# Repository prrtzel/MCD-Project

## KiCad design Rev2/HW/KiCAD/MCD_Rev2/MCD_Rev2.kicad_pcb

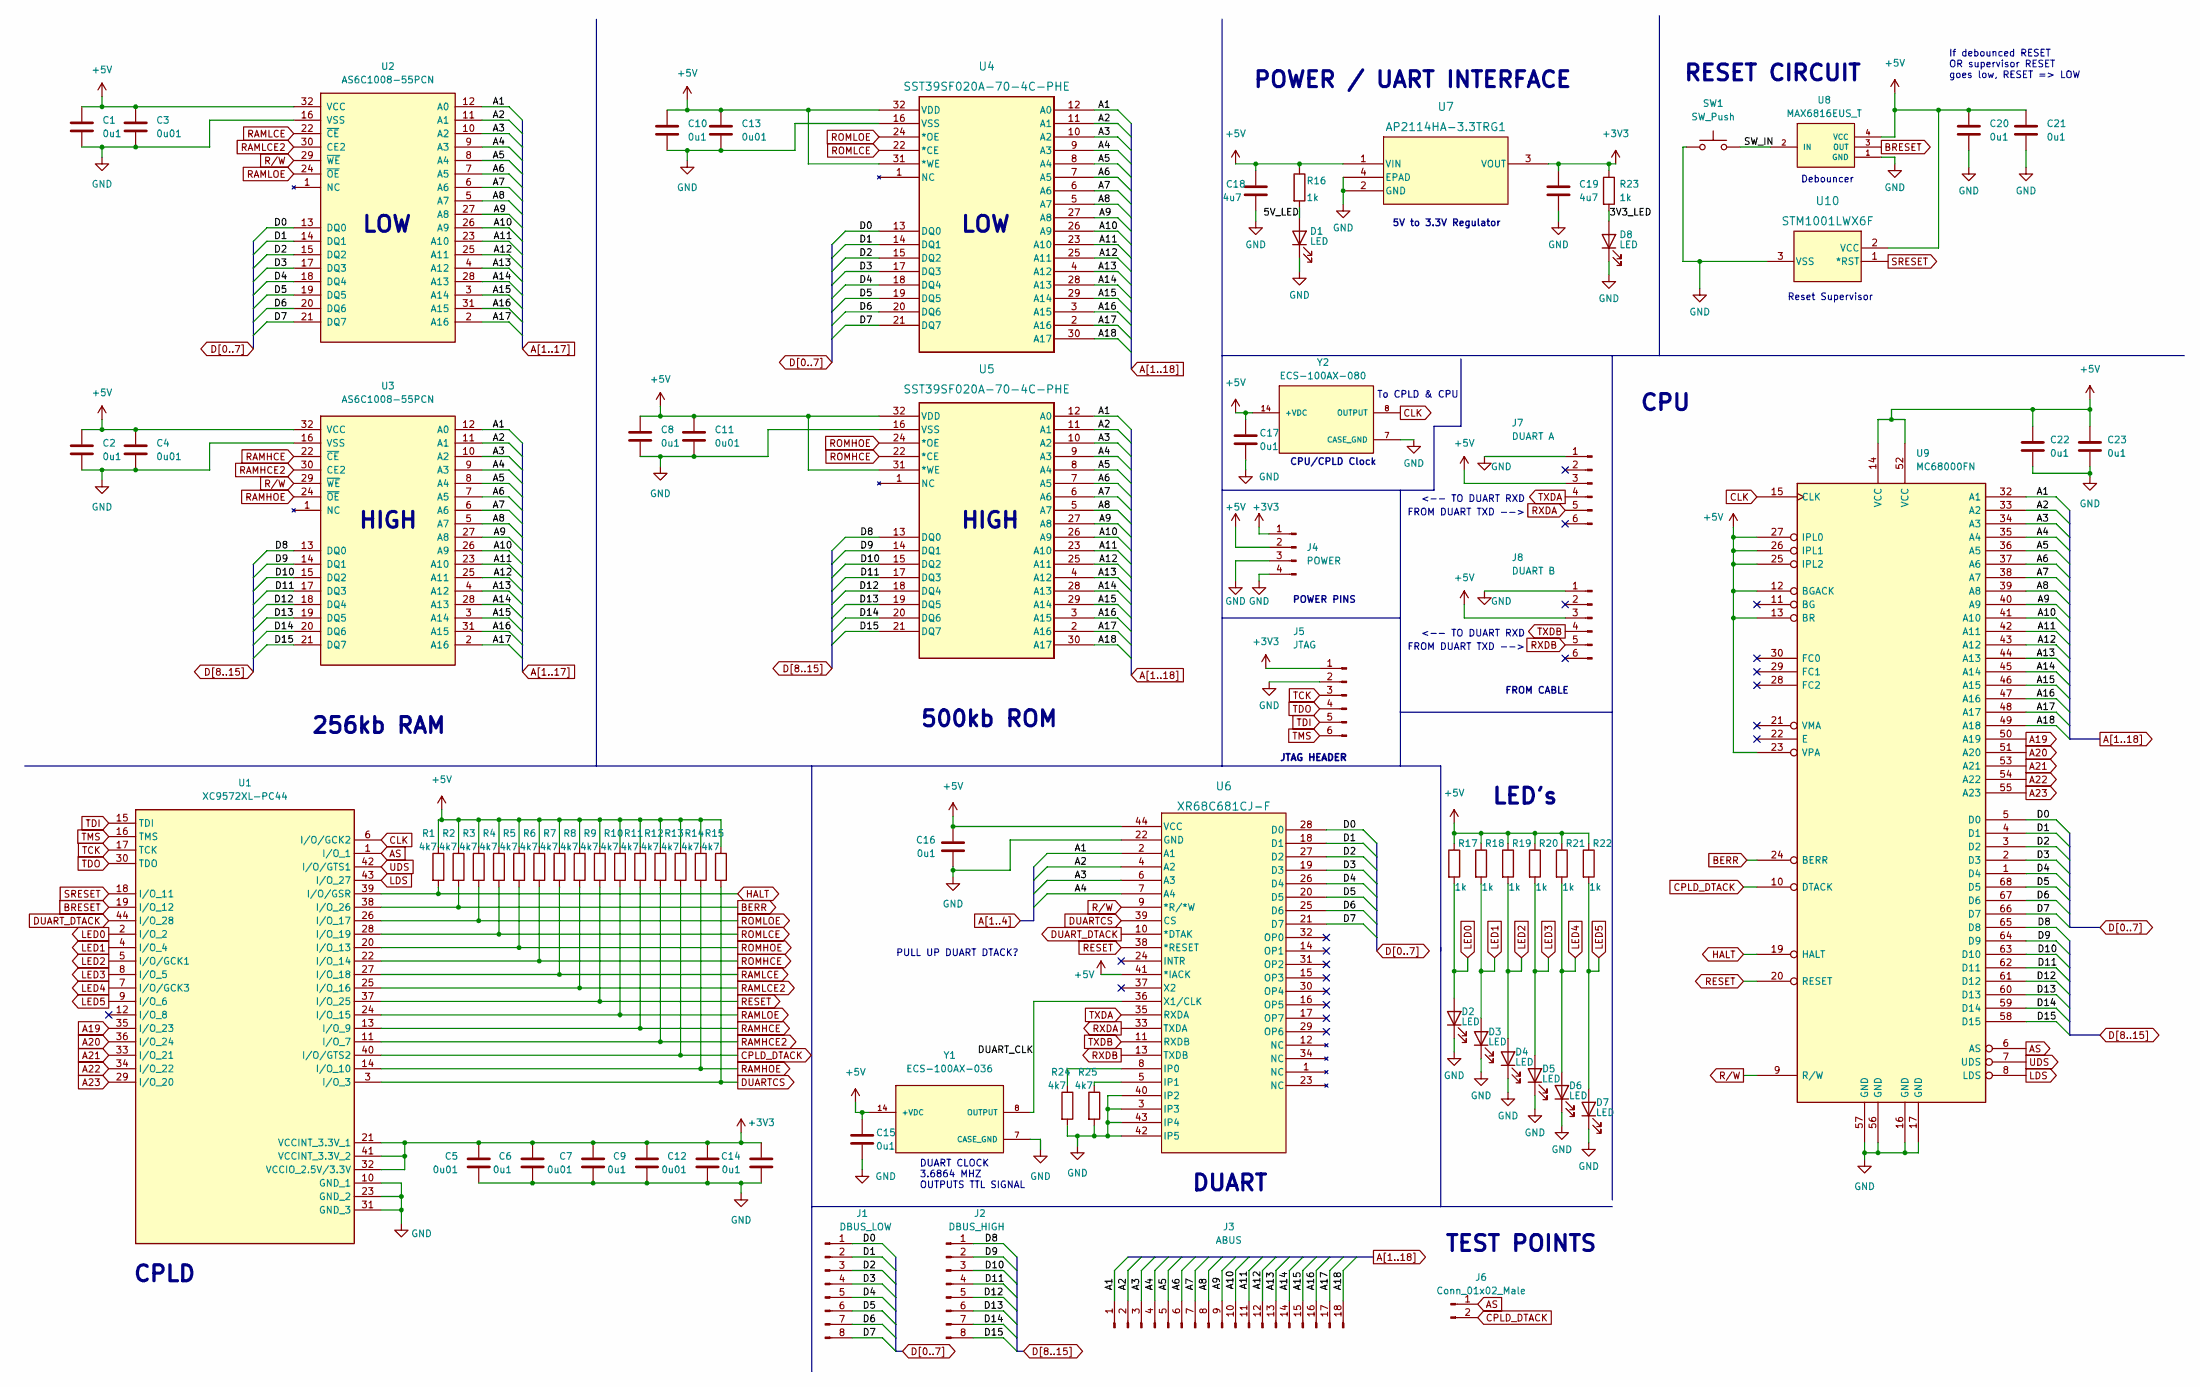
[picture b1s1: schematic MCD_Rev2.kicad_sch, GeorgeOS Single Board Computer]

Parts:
C1, C2, C6, C8, C9, C10, C14, C15, C16, C17, C20, C21, C22, C23: 0u1; C_0805_2012Metric_Pad1.18x1.45mm_HandSolder
C3, C4, C5, C7, C11, C12, C13: 0u01; C_0805_2012Metric_Pad1.18x1.45mm_HandSolder
C18, C19: 4u7; C_0805_2012Metric_Pad1.18x1.45mm_HandSolder
D1, D2, D3, D4, D5, D6, D7, D8: LED; LED_0805_2012Metric_Pad1.15x1.40mm_HandSolder
J1: DBUS_LOW; CON8_1X8_TU_HTS_SAI
J2: DBUS_HIGH; CON8_1X8_TU_HTS_SAI
J3: ABUS; CON18_2X9_TU_HTS_SAI
J4: POWER; CON4_1X4_TU_HTS_SAI
J5: JTAG; CON6_1X6_TU_HTS_SAI
J6: Conn_01x02_Male; CON2_1X2_TU_HTS_SAI
J7: DUART A; CON6_1X6_TU_HTS_SAI
J8: DUART B; CON6_1X6_TU_HTS_SAI
R1, R2, R3, R4, R5, R6, R7, R8, R9, R10, R11, R12, R13, R14, R15, R24, R25: 4k7; R_0805_2012Metric_Pad1.20x1.40mm_HandSolder
R16, R17, R18, R19, R20, R21, R22, R23: 1k; R_0805_2012Metric_Pad1.20x1.40mm_HandSolder
SW1: SW_Push; SW_PUSH_6mm
U1: XC9572XL-PC44; TO_11B1-RK-TP_3MM
U2, U3: AS6C1008-55PCN; PDIP32_PH_SST_MCH; PARTREV v1.0
U4, U5: SST39SF020A-70-4C-PHE; PDIP32_PH_SST_MCH
U6: XR68C681CJ-F; TO_11B1-RK-TP_3MM
U7: AP2114HA-3.3TRG1; SOT-223_DIO-L
U8: MAX6816EUS_T; SOT-143_Handsoldering
U9: MC68000FN; 3M_8468-11B1-RK-TP
U10: STM1001LWX6F; SOT-23_STM-L
Y1: ECS-100AX-036; OSC_ECS-100AX-036
Y2: ECS-100AX-080; OSC_ECS-100AX-080

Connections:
+3V3: C5.1, C6.1, C7.1, C9.1, C12.1, C14.1, C19.1, J4.1, J5.1, R23.1, U1.21 (VCCINT_3.3V_1), U1.32 (VCCIO_2.5V/3.3V), U1.41 (VCCINT_3.3V_2), U7.3 (VOUT)
+5V: C1.1, C2.1, C3.1, C4.1, C8.1, C10.1, C11.1, C13.1, C15.1, C16.1, C17.1, C18.1, C20.1, C21.1, C22.1, C23.1, J4.2, J7.3, J8.3, R1.1, R2.1, R3.1, R4.1, R5.1, R6.1, R7.1, R8.1, R9.1, R10.1, R11.1, R12.1, R13.1, R14.1, R15.1, R16.1, R17.1, R18.1, R19.1, R20.1, R21.1, R22.1, U2.32 (VCC), U3.32 (VCC), U4.31 (*WE), U4.32 (VDD), U5.31 (*WE), U5.32 (VDD), U6.41 (*IACK), U6.44 (VCC), U7.1 (VIN), U8.4 (VCC), U9.12 (BGACK), U9.13 (BR), U9.14 (VCC), U9.23 (VPA), U9.25 (IPL2), U9.26 (IPL1), U9.27 (IPL0), U9.52 (VCC), U10.2 (VCC), Y1.14 (+VDC), Y2.14 (+VDC)
/3V3_LED: D8.2 (A), R23.2
/5V_LED: D1.2 (A), R16.2
/DUART_CLK: U6.36 (X1/CLK), Y1.8 (OUTPUT)
/SW_IN: SW1.2, U8.2 (IN)
A1: J3.1, U2.12 (A0), U3.12 (A0), U4.12 (A0), U5.12 (A0), U6.2 (A1), U9.32 (A1)
A2: J3.2, U2.11 (A1), U3.11 (A1), U4.11 (A1), U5.11 (A1), U6.4 (A2), U9.33 (A2)
A3: J3.3, U2.10 (A2), U3.10 (A2), U4.10 (A2), U5.10 (A2), U6.6 (A3), U9.34 (A3)
A4: J3.4, U2.9 (A3), U3.9 (A3), U4.9 (A3), U5.9 (A3), U6.7 (A4), U9.35 (A4)
A5: J3.5, U2.8 (A4), U3.8 (A4), U4.8 (A4), U5.8 (A4), U9.36 (A5)
A6: J3.6, U2.7 (A5), U3.7 (A5), U4.7 (A5), U5.7 (A5), U9.37 (A6)
A7: J3.7, U2.6 (A6), U3.6 (A6), U4.6 (A6), U5.6 (A6), U9.38 (A7)
A8: J3.8, U2.5 (A7), U3.5 (A7), U4.5 (A7), U5.5 (A7), U9.39 (A8)
A9: J3.9, U2.27 (A8), U3.27 (A8), U4.27 (A8), U5.27 (A8), U9.40 (A9)
A10: J3.10, U2.26 (A9), U3.26 (A9), U4.26 (A9), U5.26 (A9), U9.41 (A10)
A11: J3.11, U2.23 (A10), U3.23 (A10), U4.23 (A10), U5.23 (A10), U9.42 (A11)
A12: J3.12, U2.25 (A11), U3.25 (A11), U4.25 (A11), U5.25 (A11), U9.43 (A12)
A13: J3.13, U2.4 (A12), U3.4 (A12), U4.4 (A12), U5.4 (A12), U9.44 (A13)
A14: J3.14, U2.28 (A13), U3.28 (A13), U4.28 (A13), U5.28 (A13), U9.45 (A14)
A15: J3.15, U2.3 (A14), U3.3 (A14), U4.29 (A14), U5.29 (A14), U9.46 (A15)
A16: J3.16, U2.31 (A15), U3.31 (A15), U4.3 (A15), U5.3 (A15), U9.47 (A16)
A17: J3.17, U2.2 (A16), U3.2 (A16), U4.2 (A16), U5.2 (A16), U9.48 (A17)
A18: J3.18, U4.30 (A17), U5.30 (A17), U9.49 (A18)
A19: U1.35 (I/O_23), U9.50 (A19)
A20: U1.36 (I/O_24), U9.51 (A20)
A21: U1.33 (I/O_21), U9.53 (A21)
A22: U1.34 (I/O_22), U9.54 (A22)
A23: U1.29 (I/O_20), U9.55 (A23)
AS: J6.1, U1.1 (I/O_1), U9.6 (AS)
BERR: R2.2, U1.38 (I/O_26), U9.24 (BERR)
BRESET: U1.19 (I/O_12), U8.3 (OUT)
CLK: U1.6 (I/O/GCK2), U9.15 (CLK), Y2.8 (OUTPUT)
CPLD_DTACK: J6.2, R13.2, U1.40 (I/O/GTS2), U9.10 (DTACK)
D0: J1.1, U2.13 (DQ0), U4.13 (DQ0), U6.28 (D0), U9.5 (D0)
D1: J1.2, U2.14 (DQ1), U4.14 (DQ1), U6.18 (D1), U9.4 (D1)
D2: J1.3, U2.15 (DQ2), U4.15 (DQ2), U6.27 (D2), U9.3 (D2)
D3: J1.4, U2.17 (DQ3), U4.17 (DQ3), U6.19 (D3), U9.2 (D3)
D4: J1.5, U2.18 (DQ4), U4.18 (DQ4), U6.26 (D4), U9.1 (D4)
D5: J1.6, U2.19 (DQ5), U4.19 (DQ5), U6.20 (D5), U9.68 (D5)
D6: J1.7, U2.20 (DQ6), U4.20 (DQ6), U6.25 (D6), U9.67 (D6)
D7: J1.8, U2.21 (DQ7), U4.21 (DQ7), U6.21 (D7), U9.66 (D7)
D8: J2.1, U3.13 (DQ0), U5.13 (DQ0), U9.65 (D8)
D9: J2.2, U3.14 (DQ1), U5.14 (DQ1), U9.64 (D9)
D10: J2.3, U3.15 (DQ2), U5.15 (DQ2), U9.63 (D10)
D11: J2.4, U3.17 (DQ3), U5.17 (DQ3), U9.62 (D11)
D12: J2.5, U3.18 (DQ4), U5.18 (DQ4), U9.61 (D12)
D13: J2.6, U3.19 (DQ5), U5.19 (DQ5), U9.60 (D13)
D14: J2.7, U3.20 (DQ6), U5.20 (DQ6), U9.59 (D14)
D15: J2.8, U3.21 (DQ7), U5.21 (DQ7), U9.58 (D15)
DUARTCS: R15.2, U1.3 (I/O_3), U6.39 (CS)
DUART_DTACK: U1.44 (I/O_28), U6.10 (*DTAK)
GND: C1.2, C2.2, C3.2, C4.2, C5.2, C6.2, C7.2, C8.2, C9.2, C10.2, C11.2, C12.2, C13.2, C14.2, C15.2, C16.2, C17.2, C18.2, C19.2, C20.2, C21.2, C22.2, C23.2, D1.1 (K), D2.1 (K), D3.1 (K), D4.1 (K), D5.1 (K), D6.1 (K), D7.1 (K), D8.1 (K), J4.3, J4.4, J5.2, J7.1, J8.1, R24.2, R25.2, SW1.1, U1.10 (GND_1), U1.23 (GND_2), U1.31 (GND_3), U2.16 (VSS), U3.16 (VSS), U4.16 (VSS), U5.16 (VSS), U6.3 (IP3), U6.22 (GND), U6.40 (IP2), U6.42 (IP5), U6.43 (IP4), U7.2 (GND), U7.4 (EPAD), U8.1 (GND), U9.16 (GND), U9.17 (GND), U9.56 (GND), U9.57 (GND), U10.3 (VSS), Y1.7 (CASE_GND), Y2.7 (CASE_GND)
HALT: R1.2, U1.39 (I/O/GSR), U9.19 (HALT)
LDS: U1.43 (I/O_27), U9.8 (LDS)
LED0: D2.2 (A), R17.2, U1.2 (I/O_2)
LED1: D3.2 (A), R18.2, U1.4 (I/O_4)
LED2: D4.2 (A), R19.2, U1.5 (I/O/GCK1)
LED3: D5.2 (A), R20.2, U1.8 (I/O_5)
LED4: D6.2 (A), R21.2, U1.7 (I/O/GCK3)
LED5: D7.2 (A), R22.2, U1.9 (I/O_6)
unnamed: R25.1, U6.5 (IP1)
unnamed: R24.1, U6.8 (IP0)
RAMHCE: R11.2, U1.13 (I/O_9), U3.22 (~CE)
RAMHCE2: R12.2, U1.11 (I/O_7), U3.30 (CE2)
RAMHOE: R14.2, U1.14 (I/O_10), U3.24 (~OE)
RAMLCE: R7.2, U1.27 (I/O_18), U2.22 (~CE)
RAMLCE2: R8.2, U1.25 (I/O_16), U2.30 (CE2)
RAMLOE: R10.2, U1.24 (I/O_15), U2.24 (~OE)
RESET: R9.2, U1.37 (I/O_25), U6.38 (*RESET), U9.20 (RESET)
ROMHCE: R6.2, U1.22 (I/O_14), U5.22 (*CE)
ROMHOE: R5.2, U1.20 (I/O_13), U5.24 (*OE)
ROMLCE: R4.2, U1.28 (I/O_19), U4.22 (*CE)
ROMLOE: R3.2, U1.26 (I/O_17), U4.24 (*OE)
RXDA: J7.5, U6.33 (TXDA)
RXDB: J8.5, U6.13 (TXDB)
R/W: U2.29 (~WE), U3.29 (~WE), U6.9 (*R/*W), U9.9 (R/W)
SRESET: U1.18 (I/O_11), U10.1 (*RST)
TCK: J5.3, U1.17 (TCK)
TDI: J5.5, U1.15 (TDI)
TDO: J5.4, U1.30 (TDO)
TMS: J5.6, U1.16 (TMS)
TXDA: J7.4, U6.35 (RXDA)
TXDB: J8.4, U6.11 (RXDB)
UDS: U1.42 (I/O/GTS1), U9.7 (UDS)

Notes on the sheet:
LOW
DUART
<-- TO DUART RXD
FROM DUART TXD -->
CPLD
To CPLD & CPU
256kb RAM
Debouncer
CPU/CPLD Clock
HIGH
JTAG HEADER
PULL UP DUART DTACK?
DUART CLOCK 3.6864 MHZ OUTPUTS TTL SIGNAL
POWER PINS
TEST POINTS
LED's
FROM CABLE
HIGH
5V to 3.3V Regulator
RESET CIRCUIT
Reset Supervisor
POWER / UART INTERFACE
If debounced RESET OR supervisor RESET goes low, RESET => LOW
CPU
500kb ROM

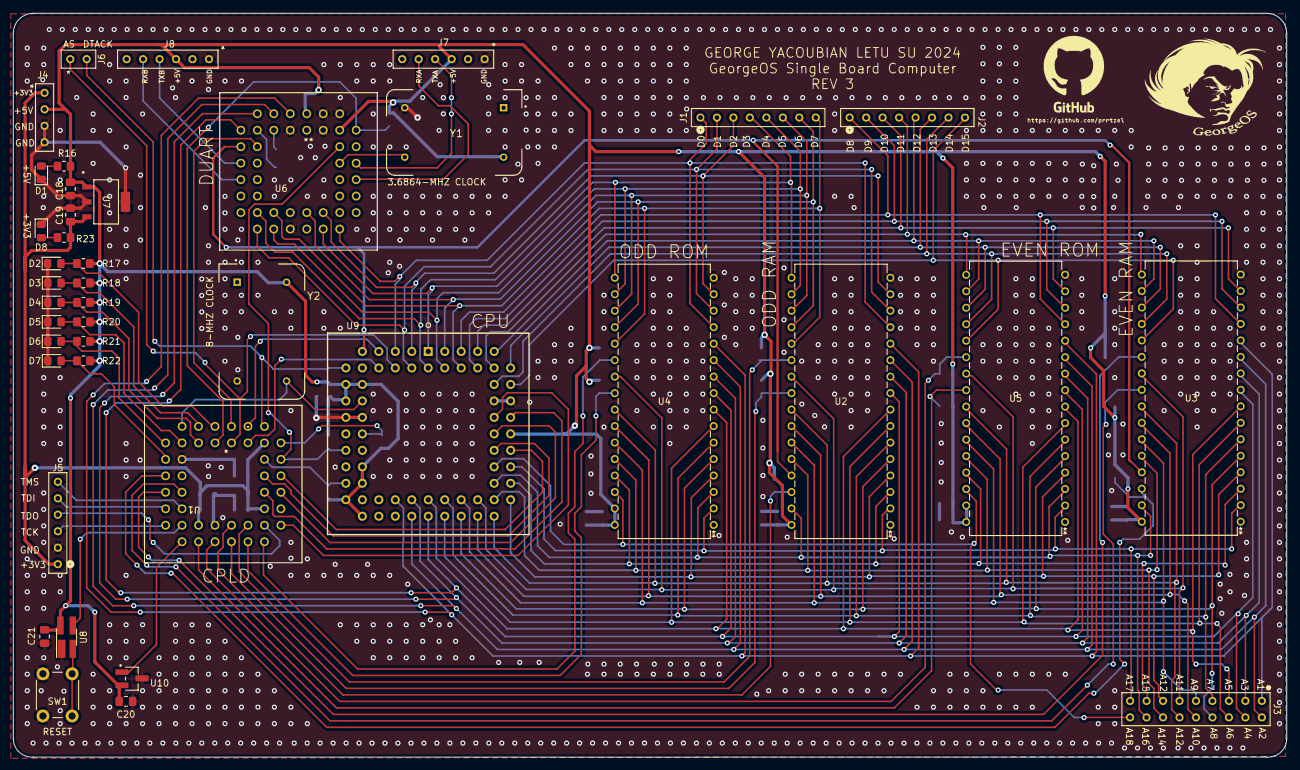
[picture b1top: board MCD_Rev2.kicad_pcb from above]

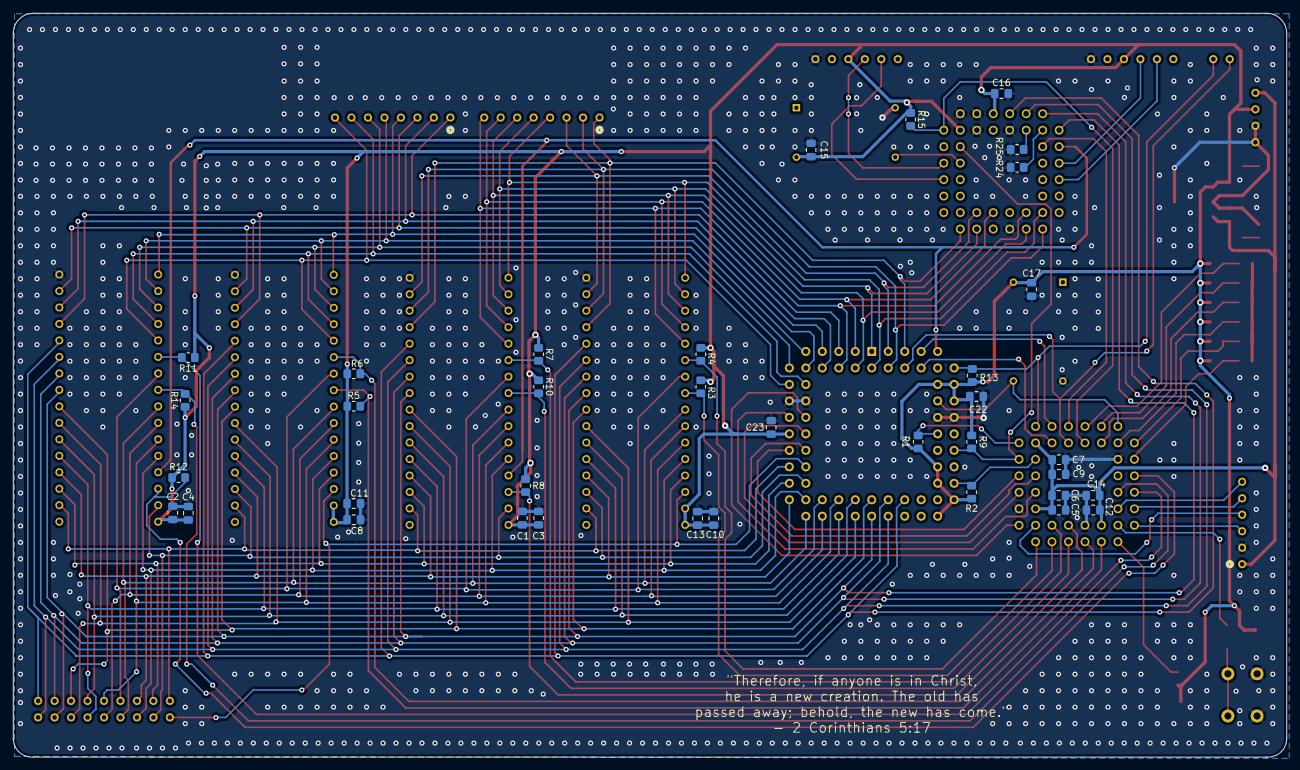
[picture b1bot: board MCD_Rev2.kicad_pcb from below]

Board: 2 copper layers, 196.3 x 114.7 mm, 77 parts (36 on the bottom side), 85 nets.

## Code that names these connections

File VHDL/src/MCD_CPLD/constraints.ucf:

NET SRESET	    LOC=P18;
NET BRESET	    LOC=P19;
NET DUART_DTACK LOC=P44;
NET HALT        LOC=P39;
NET BERR        LOC=P38;
NET RESET       LOC=P37;
NET CPU_DTACK   LOC=P40;
NET DUARTCS     LOC=P3;

NET ABUS<0>	    LOC=P35;
NET ABUS<1>	    LOC=P36;

NET LED<0>	    LOC=P2;
NET LED<1>	    LOC=P4;
NET LED<2>	    LOC=P5;
NET LED<3>	    LOC=P8;
NET LED<4>	    LOC=P7;
NET LED<5>	    LOC=P9;

NET CLK         LOC=P6;
NET AS          LOC=P1;
NET UDS         LOC=P42;
NET LDS         LOC=p43;

NET ROMLOE      LOC=P26;
NET ROMLCE      LOC=P28;

NET ROMHOE      LOC=P20;
NET ROMHCE      LOC=P22;

NET RAMLCE      LOC=P27;
NET RAMLCE2     LOC=P25;
NET RAMLOE      LOC=P24;

NET RAMHCE      LOC=P13;
NET RAMHCE2     LOC=P11;
NET RAMHOE      LOC=P14;

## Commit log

2023-11-21 added assembly file
2023-11-21 Updated and working In2MCD Final for 1 and 2
2023-11-21 added string to hex conversion (part 3)
2023-11-21 added exception handling and cleaned up code
2023-11-21 Cleaned up code, added stack register management for subroutines
2023-11-21 Changed .b to .l bug in hex to ascii hex
2023-11-21 added tests, string to hex not working yet
2023-11-28 fixed test routine, hex2ascii now takes "0000"
2023-12-04 fixed bugs
2023-12-11 added support for windows batch file in ez68k
2023-12-11 code no compiles to C
2023-12-11 linker wip
2023-12-11 linker combines files; c + asm wip
2023-12-12 linker now links
2023-12-12 print function implemented
2023-12-12 cleanup
2023-12-12 added stack control for serial print function
2023-12-12 added very much improved file structure :) caution: jank makefile
2023-12-12 added stdio lib and a getstring function
2023-12-12 added ascii hex to hex function
2023-12-12 added all conversions from intro to MCD final in C
2023-12-12 added a print word function for conversion
2023-12-12 added main menuand supprt for option 1
2023-12-12 done for day...I need to make a malloc :(
2023-12-13 fixed choice 1 not reading multiple instances
2023-12-13 Backspace is now supported, but sprint was changed so now it does not lf cr
2023-12-13 enter key is now supported using \r not \n
2023-12-13 backspace now tracks position of cursor
2023-12-13 added address parser
2023-12-13 Morg now reads from memory!!!
2023-12-13 scratch last, prints 2 bytes instead of one
2023-12-13 NOW IT READS A BYTE FROM MEM
2023-12-13 read memory now inputs long word addresses and outputs a byte
2023-12-13 reverted back due to strange behavior
2023-12-14 now reads and writes, Note: multiple inputs need to be put in buffer
2023-12-14 more cleanup
2023-12-15 now can use inline asm
2023-12-15 read reg wip
2024-01-31 ROUGH DRAFT SCHEMATIC
2024-02-02 updated GeorgeOS makefile
2024-02-12 last revision with vbcc
2024-02-16 working on pcb
2024-02-16 I NEED TO TAKE BRAKE
2024-02-16 finished data bus
2024-02-16 DO NOT CHANGE THIS BISCUIT PARAMETERS
2024-02-16 HALF OF ABUS
2024-02-17 abus done, working on dbus
2024-02-17 abus and dbus done
2024-02-17 abus and dbus double done
2024-02-17 updated pcb
2024-02-17 AHHH THE BUS WAS NOT CONNECTD THAMK YOU GF FOR POINTYING THAT ORUT
2024-02-17 KICAD WAS GOOFY! anyuways decode bus is done, routing control bus
2024-02-17 control bus almost done
2024-02-17 everything but power connected
2024-02-18 FINISHED!!! (I THINK)
2024-02-18 REV 1 OUT
2024-02-18 board and parts ordered
2024-02-26 IT FREAKING LINKS AND WORKS
2024-03-04 linker now sees main symbol
2024-03-04 sprint now works
2024-03-04 changed linker command and make file to link multiple files, headers now work
2024-03-12 worked on string stuff
2024-03-12 getString and getChar now work and put strings in an input buffer
2024-03-13 adding conversions
2024-03-13 conversion works
2024-03-13 get string now takes a buffer as an input instead of a static one in the stdio lib
2024-03-13 read memory now works
2024-03-13 read mem now prints value instead of returning one
2024-03-13 read mem and memdump now work
2024-03-13 read and write to memory implemented
2024-03-13 created commands documentation
2024-03-14 menu
2024-03-23 changed xc9572xl schematic symbol from vq44 to pc44
2024-03-24 finished pcb, not checked yet but drc is good
2024-03-25 now converts to hex to bin and bin to hex
2024-03-28 monitor now reads and writes to memory
2024-04-03 added read rregiste, working on write reg
2024-04-03 eoiwlgn
2024-04-03 morg now reads and writes to registers
2024-04-03 need to fix read reg, will not read if first byte is F
2024-04-06 finished duart test code, not tested
2024-04-06 cleaanup cleaan up everybody everywhere...
2024-04-09 added vector stuff in test rx now rwx for ram
2024-04-09 cleaned up ld
2024-04-15 changed adecodiign
2024-04-19 rom and ram test work, working on integrating bare bones C
2024-04-19 putchar works in asm
2024-04-19 back to og state, can recive but not transmit in getchar
2024-04-25 wrapping it up for SP2024, now for Rev2
2024-05-27 added morg files
2024-06-10 started via stitching
2024-06-11 finished signals and power, need to via stitch
2024-06-12 spaced out traces
2024-06-12 spaced out traces EVEN MORE
2024-06-12 filled in POURS
2024-06-13 added via stitching, now adjusting silkscreen
2024-06-13 via stitching done, adjusting silscreen
2024-06-13 pcb draft done, waiting for input from profreshonal
2024-06-13 progress on morg startup biz
2024-06-13 variables now go where they should!!
2024-06-13 strings now string
2024-06-13 get char for sim implemented
2024-06-14 make is happy everything builds and string compare is implemented
2024-06-17 memory is still a bit wack, making conversions so that we can debug that
2024-06-17 MEMORY WORKS!! extern symbols MUST NOT BE DECLARED AS POINTERS
2024-06-17 correction, data section works, bss not set to 0
2024-06-17 bss works, variables need to be static
2024-06-17 started parsing and modified cmp_str
2024-06-17 fixed cmp_str
2024-06-18 morg implemented, need srec things
2024-06-18 organization
2024-06-18 worked on srec parsing
2024-06-19 load_srec implemented
2024-06-19 run srec implemented
2024-06-19 morg rough draft finished
2024-06-19 finished pcb
2024-06-19 generated gerber files for rev3
2024-06-19 docs
2024-06-21 added support for better commands and finished pcb rev3
2024-06-26 finished bat scripts for automating odd and even memory bin files
2024-06-26 batch scripts now open xgpro and load file
2024-06-28 working on getting cpld to work
